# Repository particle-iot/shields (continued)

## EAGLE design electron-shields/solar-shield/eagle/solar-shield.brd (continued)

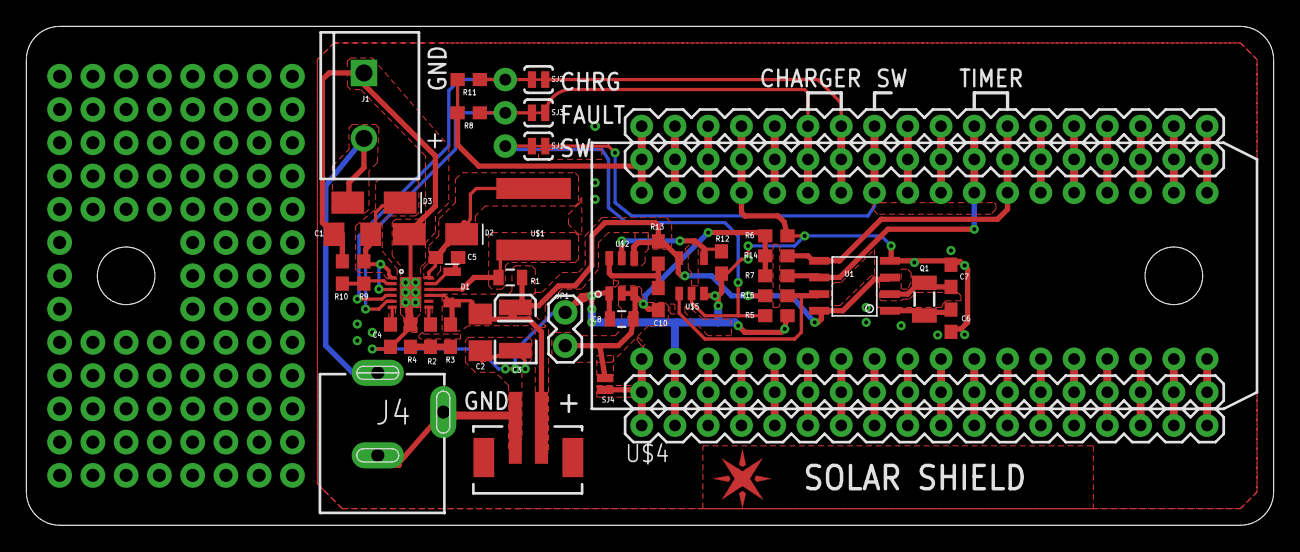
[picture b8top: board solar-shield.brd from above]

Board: 2 copper layers, 95.2 x 38.1 mm, 43 parts (0 on the bottom side), 54 nets.

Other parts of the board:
U$3: SPARK_LOGO_PLUS_PLANE

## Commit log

2013-04-02 Initial core shield shield Eagle files for review
2013-04-02 Re-routed traces
2013-04-02 Added switch, removed AREF, redrew some traces.
2013-04-02 Deleted and ignored unnecessary files
2013-04-02 Moved Shield Shield into its own directory
2013-04-02 Created gerber files for Shield Shield
2013-04-03 Created PIR and Battery Shields for Spark Core
2013-04-05 Reviewed battery shield and PIR shield. Good to go.
2013-04-05 Added programmer shield
2013-04-05 Generated .zip files for production at HQPCB. Design unchanged.
2013-04-08 WIP: Created infinity camera from Shield Shield template.
2013-04-08 Added missing files from last commit.
2013-04-08 Brought in the correct Shield Shield EAGLE files
2013-04-08 Made a few more changes to the LCD shield
2013-04-08 Reviewed Infinity Camera
2013-04-08 Reviewed LCD Shield
2013-04-08 Started adding transistor to the Inifinity Camera. Still needs to be finished. Generated Gerber files for the LCD Shield and had it spun up. Infinity camera gerber files need to be updated upon compl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
2013-04-10 Updated infinity camera with transistor and recreated Gerber files
2013-04-15 Created relay shield
2013-04-15 Completed relay shield schematic and board
2013-04-15 WIP: Moved relay shield from programmer shield folder (last commit was bad)
2013-04-15 Fixed programmer shield
2013-04-15 Created gerber files for relay shield
2013-04-16 Updated Shield Shield so Core is not underneath Shield
2013-04-17 Fixed LCD Shield, upgraded to v0.2
2013-07-23 added the new shield designs
2013-07-24 Generated Gerbers
    Generated gerbers for the Relay Shield, Shield Shield, and Programmer
    Shield.
2013-07-25 cleaned up the folders of all updated shields and created files for battery shield
2013-07-25 rearranged battery shield folder contents
2013-07-27 Cleaned up Shield Shield BOM
    Nothing major--just separated the EAGLE export in the BOM file.
2013-07-30 updated the battery shield and created the BOM
2013-07-30 updated datasheets folder
2013-07-30 connected the DGND and GND nets manually on the PCB
2013-07-31 Shield Shield Stencil Gerbers
2013-07-31 Updated Shield BOMs and Battery Shield Gerbers
    Generated gerbers for PCB and Stencil production for the Battery Shield.
    Updated the BOMs of all four shields to quoteable format. Mohit, I
    need help from you filling out some of the final fields, and
    understanding which component P/Ns are critical to the board design.
2013-07-31 Add license to README
2013-08-03 Updated BOMs
2013-08-16 updated shield BOMs and boards
2013-08-18 Updated Gerber Files
    For all the shields.
2013-08-19 updated changes to the battery shield
2013-08-24 updated battery shield
2013-08-24 Major hoverhaul to the Relay Shield
2013-08-24 Updated Gerbers for all the shields
2013-08-25 Re-Generated Gerber Files
    The old ones weren't importing well into my Gerber viewer.
2013-08-26 rearranged folders and added the version with bigger inductor
2013-08-26 remove redundant files
2013-08-26 remove redundant Gerber files
2013-08-27 updated the test position on the battery shield
2013-08-27 updated gerbers for battery and realy shields
2013-09-04 added 3d model for sshield
2013-09-05 added resistors to the sshield and some minor edits
2013-09-05 changed the voltage regulator on the relay shield
2013-09-05 updated BOM for the relay shield
2013-09-06 Updated Gerbers
    For Shield shield and battery shield
2013-09-07 Generated Relay Shield Gerbers
    Updated after the VR change
2013-09-13 updated part designators as per to Sir William's request
2013-11-19 added license file
2013-11-19 added license info to all design files
2013-11-20 Updated BOMs for all Shields and MKit
    See above
2014-01-02 Ignored .DS_Store
2014-01-08 updated sshield and pshield gerbers
2014-01-08 updated battery shield gerbers to v201
2014-01-08 updated relay shield gerbers to v201
2014-03-26 Battery Shield Support Stuff for AQS
    Assembly diagram, stencil, BOM
2014-07-08 PDF files for Schematics
2014-08-19 deleted stale files
2014-08-19 updated relay shield files to v210
2014-08-19 removed old gerber files
2014-08-19 updated the bom and designator for regulator
2014-08-20 updated designators and bom
2015-07-09 added new photon shield design files
2015-07-09 cleanup
2015-07-10 Adding photon schematics PDFs
    This allows people to view the schematics without any software installed.
2015-07-10 added rev numbers to schematic sheets and regenerated the PDFs
2015-07-10 added missing datasheets :boom:
2015-07-17 First commit on official libraries
    Includes RelayShield
2015-07-17 ... updated JSON for RelayShield
2015-07-17 Fixed up directory structure for RelayShield
2015-07-20 added power shield library :zap:
2015-08-16 Fixed a few commands :lollipop:
2015-09-02 Typo fixes
    - just member and not members
    - awexome --> awesome
2015-09-14 added common flash commands and yosemite note
2015-09-17 Create a new folder for electron-shield
2015-09-17 Change the attribute of readme file
2015-09-18 Spelling error
2015-09-20 Add warning about pins used for JTAG
    I've been bitten several times not being able to connect the debugger because my user code uses D7 (the blue LED). Let's warn others.
2015-09-23 Added example usage of protecting JTAG pins
2015-11-08 Create a wrapper script for Particle OpenOCD
2015-11-08 make wrapper script shorter, thats the whole point of it
2016-03-08 added troubleshooting section
2016-04-05 added design files for the electron shields
2016-04-05 added accelerometer app note
2016-04-21 versioned
2016-04-22 replaced uff with SMA and changed GPS module location
2016-04-25 routing routing
2016-04-25 v002 updates and creation of future v003
2016-04-25 3v3 trace widened
2016-04-25 added version number
2016-05-05 Add top-level README and CC-BY-SA license
2016-07-15 added ublox pam-7q datasheets
2016-07-26 u-blox data sheets and hardware integration manuals
2016-07-27 added max-m8 gps and max2674 ant switch packages
2016-07-28 updated schematic and added more data sheets
2016-08-03 added patch antenna and enclosure outline
2016-08-10 added saw filter, li ion cell and routing almost complete
2016-08-11 added a nuclear reactor for power, routing done, need labels
2016-08-12 added labels in gotham font, needs aligning
2016-08-18 labeling done
2016-08-18 generated gerbers
2016-08-19 added archived blog post in troubleshooting section
2016-08-22 Updated schematic based on ublox's feedback, now on to v005
    - Added ferrite beads on TX/RX lines
    - Transistor to drive the LED
    - Changed cap value on power line of the antenna switch (0.1uF to 10pF)
2016-09-06 new gerbers made
2016-10-20 Motor shield
    This is the folder for motor shiled.
2016-11-03 created v006 for asset tracker with new RF parts
2016-11-07 v006 asset tracker gerber generated
2016-11-08 updated gerber and added 50 ohm RF trace image
2016-11-25 The silkscreen of TX and RX is wrong.
2016-12-02 corrected the labeling and added logo
2016-12-02 added bias supply to the active antenna rf trace
2016-12-02 vcc_rf trace width increased
2016-12-06 add the gerber file for v007 version
2016-12-15 Add the production gerber file
    Production gerber file from factory which need the approve from us
2016-12-15 tx rx swap on bottom silk
2016-12-15 tx rx swapped in the new gerbers
2016-12-16 create a simple RGB breakoutBoard
2016-12-16 removed artifacts left behind by git merge in the pub file
2016-12-16 generate the gerber fils for rgbBreakoutBoard
2016-12-19 update the panel gerber for reg breakoutboard
2016-12-21 add the gerber for rgb Breakoutboard
2016-12-21 update the designator for production use
    Resized some name text and move all of them close to the components for
    production use
2016-12-21 add the gerber for rgb breakout board
2017-01-18 Migrated RelayShield to v2
    All the Libraries V2 changes your body has room for!
2017-04-12 reorganized asset tracker files
2017-06-05 update the asset tracker with some modification
    1, Change the package for some cap/inductor for avoid the tombstone
    production during production.
    2, Add circle marks on those pins that
    will be used for controlling GPS or accelerometer, as weel as the grove
    connector port
    3, Change those two white connector to grove compatible
2017-06-12 update the internet button to v140.
    Add a Accelerometer footprint
    Modifiy the ground plane for Wifi optimize.
    Chnage the power supplier for the original accel to a GPIO
2017-06-16 update the design file since i catch some error from last version
2017-06-22 update power shield. add customized silkscreen
2017-06-23 update the grove connector again,make the latch face the edge of the board
2017-07-19 update the pcb file for internet button
2017-08-04 update the arrow for silkscreen
2018-01-03 org-rename
2018-01-30 Added asset tracker v2 bom
